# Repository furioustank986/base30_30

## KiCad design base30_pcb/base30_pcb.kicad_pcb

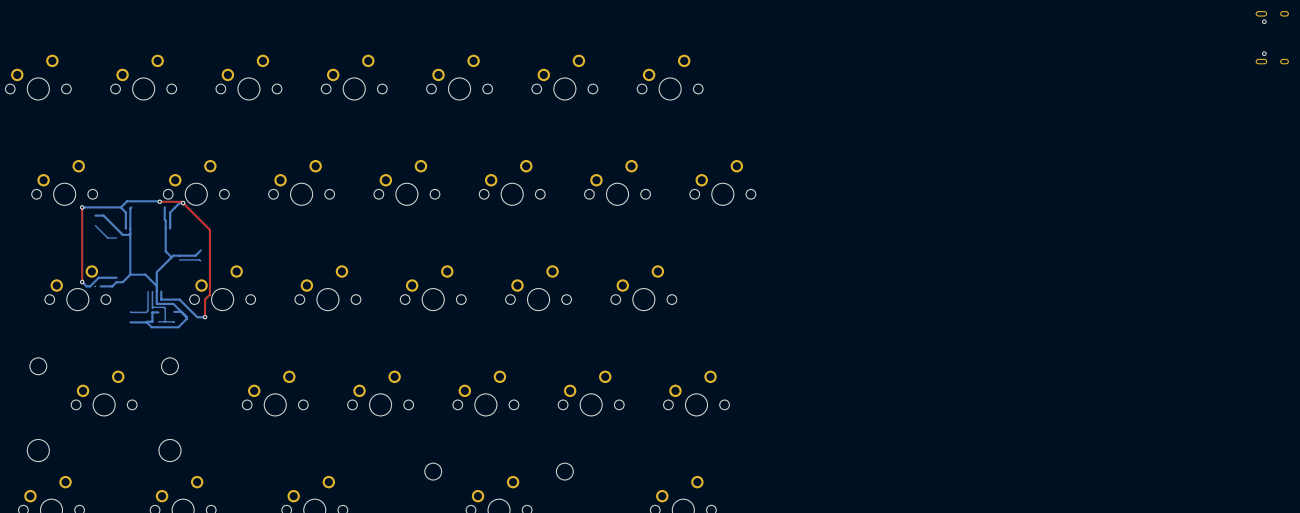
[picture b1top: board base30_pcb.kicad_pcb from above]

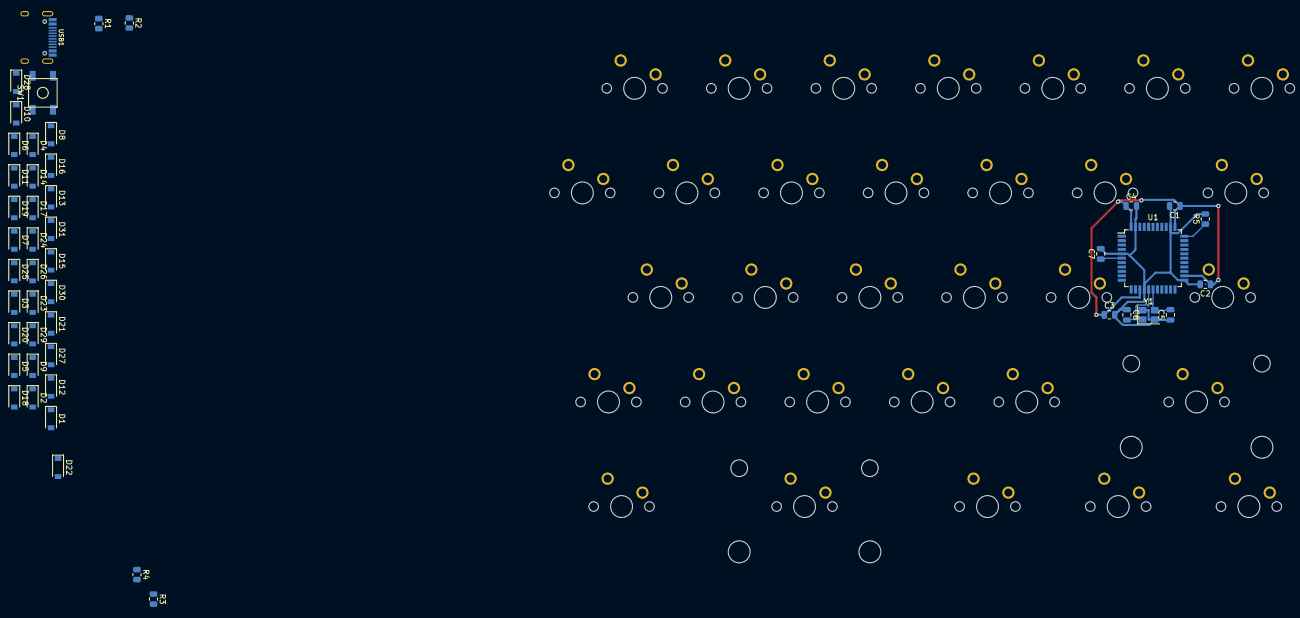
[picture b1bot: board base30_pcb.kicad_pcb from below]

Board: 2 copper layers, 78 parts (47 on the bottom side), 56 nets.

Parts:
C1, C2, C3: 0.1uF; C_0805_2012Metric
C4: 10uF; C_0805_2012Metric
C5, C6: 22pF; C_0805_2012Metric
C7: C_Small; C_0805_2012Metric
D1, D2, D3, D4, D5, D6, D7, D8, D9, D10, D11, D12, D13, D14, D15, D16, D17, D18, D19, D20, D21, D22, D23, D24, D25, D26, D27, D28, D29, D30, D31: D_Small; D_SOD-123
MX1, MX5, MX8, MX9, MX10, MX11, MX12, MX13, MX14, MX15, MX17, MX18, MX19, MX20, MX22, MX23, MX24, MX25, MX26, MX27, MX28, MX29, MX31: MX-NoLED; MXOnly-1U-NoLED
MX2: MX-NoLED; MXOnly-1.5U-NoLED
MX3: MX-NoLED; MXOnly-1.75U-NoLED
MX4, MX7, MX16, MX30: MX-NoLED; MXOnly-1.25U-NoLED
MX6, MX21: MX-NoLED; MXOnly-2.25U-NoLED
R1, R2: 5k; R_0805_2012Metric
R3, R4: 22; R_0805_2012Metric
R5: 10k; R_0805_2012Metric
SW1: SW_Push; SKQG-1155865
U1: ATmega32U4-A; TQFP-44_10x10mm_P0.8mm
USB1: HRO-TYPE-C-31-M-12; HRO-TYPE-C-31-M-12-Assembly
Y1: Crystal_GND24_Small; Crystal_SMD_3225-4Pin_3.2x2.5mm

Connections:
+5V: C1.1, C2.1, C3.1, C4.1, U1.2 (UVCC), U1.7 (VBUS), U1.14 (VCC), U1.24 (AVCC), U1.34 (VCC), U1.44 (AVCC), USB1.2 (VBUS), USB1.11 (VBUS)
/D+: R3.1, USB1.6 (DP1), USB1.8 (DP2)
/D-: R4.1, USB1.5 (DN2), USB1.7 (DN1)
/c0: MX1.1 (COL), MX2.1 (COL), MX3.1 (COL), MX4.1 (COL)
/c1: MX5.1 (COL), MX6.1 (COL), MX7.1 (COL)
/c2: MX8.1 (COL), MX9.1 (COL), MX10.1 (COL), MX11.1 (COL)
/c3: MX12.1 (COL), MX13.1 (COL), MX14.1 (COL), MX15.1 (COL), MX16.1 (COL)
/c4: MX17.1 (COL), MX18.1 (COL), MX19.1 (COL), MX20.1 (COL), MX21.1 (COL)
/c5: MX22.1 (COL), MX23.1 (COL), MX24.1 (COL), MX25.1 (COL)
/c6: MX26.1 (COL), MX27.1 (COL), MX28.1 (COL), MX29.1 (COL), MX30.1 (COL)
/r0: D1.1 (K), D5.1 (K), D8.1 (K), D12.1 (K), D17.1 (K), D22.1 (K), D26.1 (K)
/r1: D2.1 (K), D9.1 (K), D13.1 (K), D18.1 (K), D23.1 (K), D27.1 (K), D31.1 (K)
/r2: D3.1 (K), D10.1 (K), D14.1 (K), D19.1 (K), D24.1 (K), D28.1 (K)
/r3: D6.1 (K), D11.1 (K), D15.1 (K), D20.1 (K), D25.1 (K), D29.1 (K)
/r4: D4.1 (K), D7.1 (K), D16.1 (K), D21.1 (K), D30.1 (K)
GND: C1.2, C2.2, C3.2, C4.2, C5.1, C6.1, C7.2, R1.2, R2.2, R5.2, SW1.1, U1.5 (UGND), U1.15 (GND), U1.23 (GND), U1.35 (GND), U1.43 (GND), USB1.1 (GND), USB1.12 (GND), USB1.13 (SHIELD), Y1.2, Y1.4
unnamed: C5.2, U1.17 (XTAL1), Y1.3
unnamed: C6.2, U1.16 (XTAL2), Y1.1
unnamed: C7.1, U1.6 (UCAP)
unnamed: D1.2 (A), MX1.2 (ROW)
unnamed: D2.2 (A), MX2.2 (ROW)
unnamed: D3.2 (A), MX3.2 (ROW)
unnamed: D4.2 (A), MX4.2 (ROW)
unnamed: D5.2 (A), MX5.2 (ROW)
unnamed: D6.2 (A), MX6.2 (ROW)
unnamed: D7.2 (A), MX7.2 (ROW)
unnamed: D8.2 (A), MX8.2 (ROW)
unnamed: D9.2 (A), MX9.2 (ROW)
unnamed: D10.2 (A), MX10.2 (ROW)
unnamed: D11.2 (A), MX11.2 (ROW)
unnamed: D12.2 (A), MX12.2 (ROW)
unnamed: D13.2 (A), MX13.2 (ROW)
unnamed: D14.2 (A), MX14.2 (ROW)
unnamed: D15.2 (A), MX15.2 (ROW)
unnamed: D16.2 (A), MX16.2 (ROW)
unnamed: D17.2 (A), MX17.2 (ROW)
unnamed: D18.2 (A), MX18.2 (ROW)
unnamed: D19.2 (A), MX19.2 (ROW)
unnamed: D20.2 (A), MX20.2 (ROW)
unnamed: D21.2 (A), MX21.2 (ROW)
unnamed: D22.2 (A), MX22.2 (ROW)
unnamed: D23.2 (A), MX23.2 (ROW)
unnamed: D24.2 (A), MX24.2 (ROW)
unnamed: D25.2 (A), MX25.2 (ROW)
unnamed: D26.2 (A), MX26.2 (ROW)
unnamed: D27.2 (A), MX27.2 (ROW)
unnamed: D28.2 (A), MX28.2 (ROW)
unnamed: D29.2 (A), MX29.2 (ROW)
unnamed: D30.2 (A), MX30.2 (ROW)
unnamed: D31.2 (A), MX31.2 (ROW)
unnamed: R1.1, USB1.4 (CC1)
unnamed: R2.1, USB1.10 (CC2)
unnamed: R3.2, U1.4 (D+)
unnamed: R4.2, U1.3 (D-)
unnamed: R5.1, U1.33 (~HWB/PE2)
unnamed: SW1.2, U1.13 (~RESET)

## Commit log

2022-12-24 added layout json/jpg, matrix json, and qmk code
2022-12-25 added case files. TODO: Make cover, usb holes, magnet.
2022-12-27 added pcb files
